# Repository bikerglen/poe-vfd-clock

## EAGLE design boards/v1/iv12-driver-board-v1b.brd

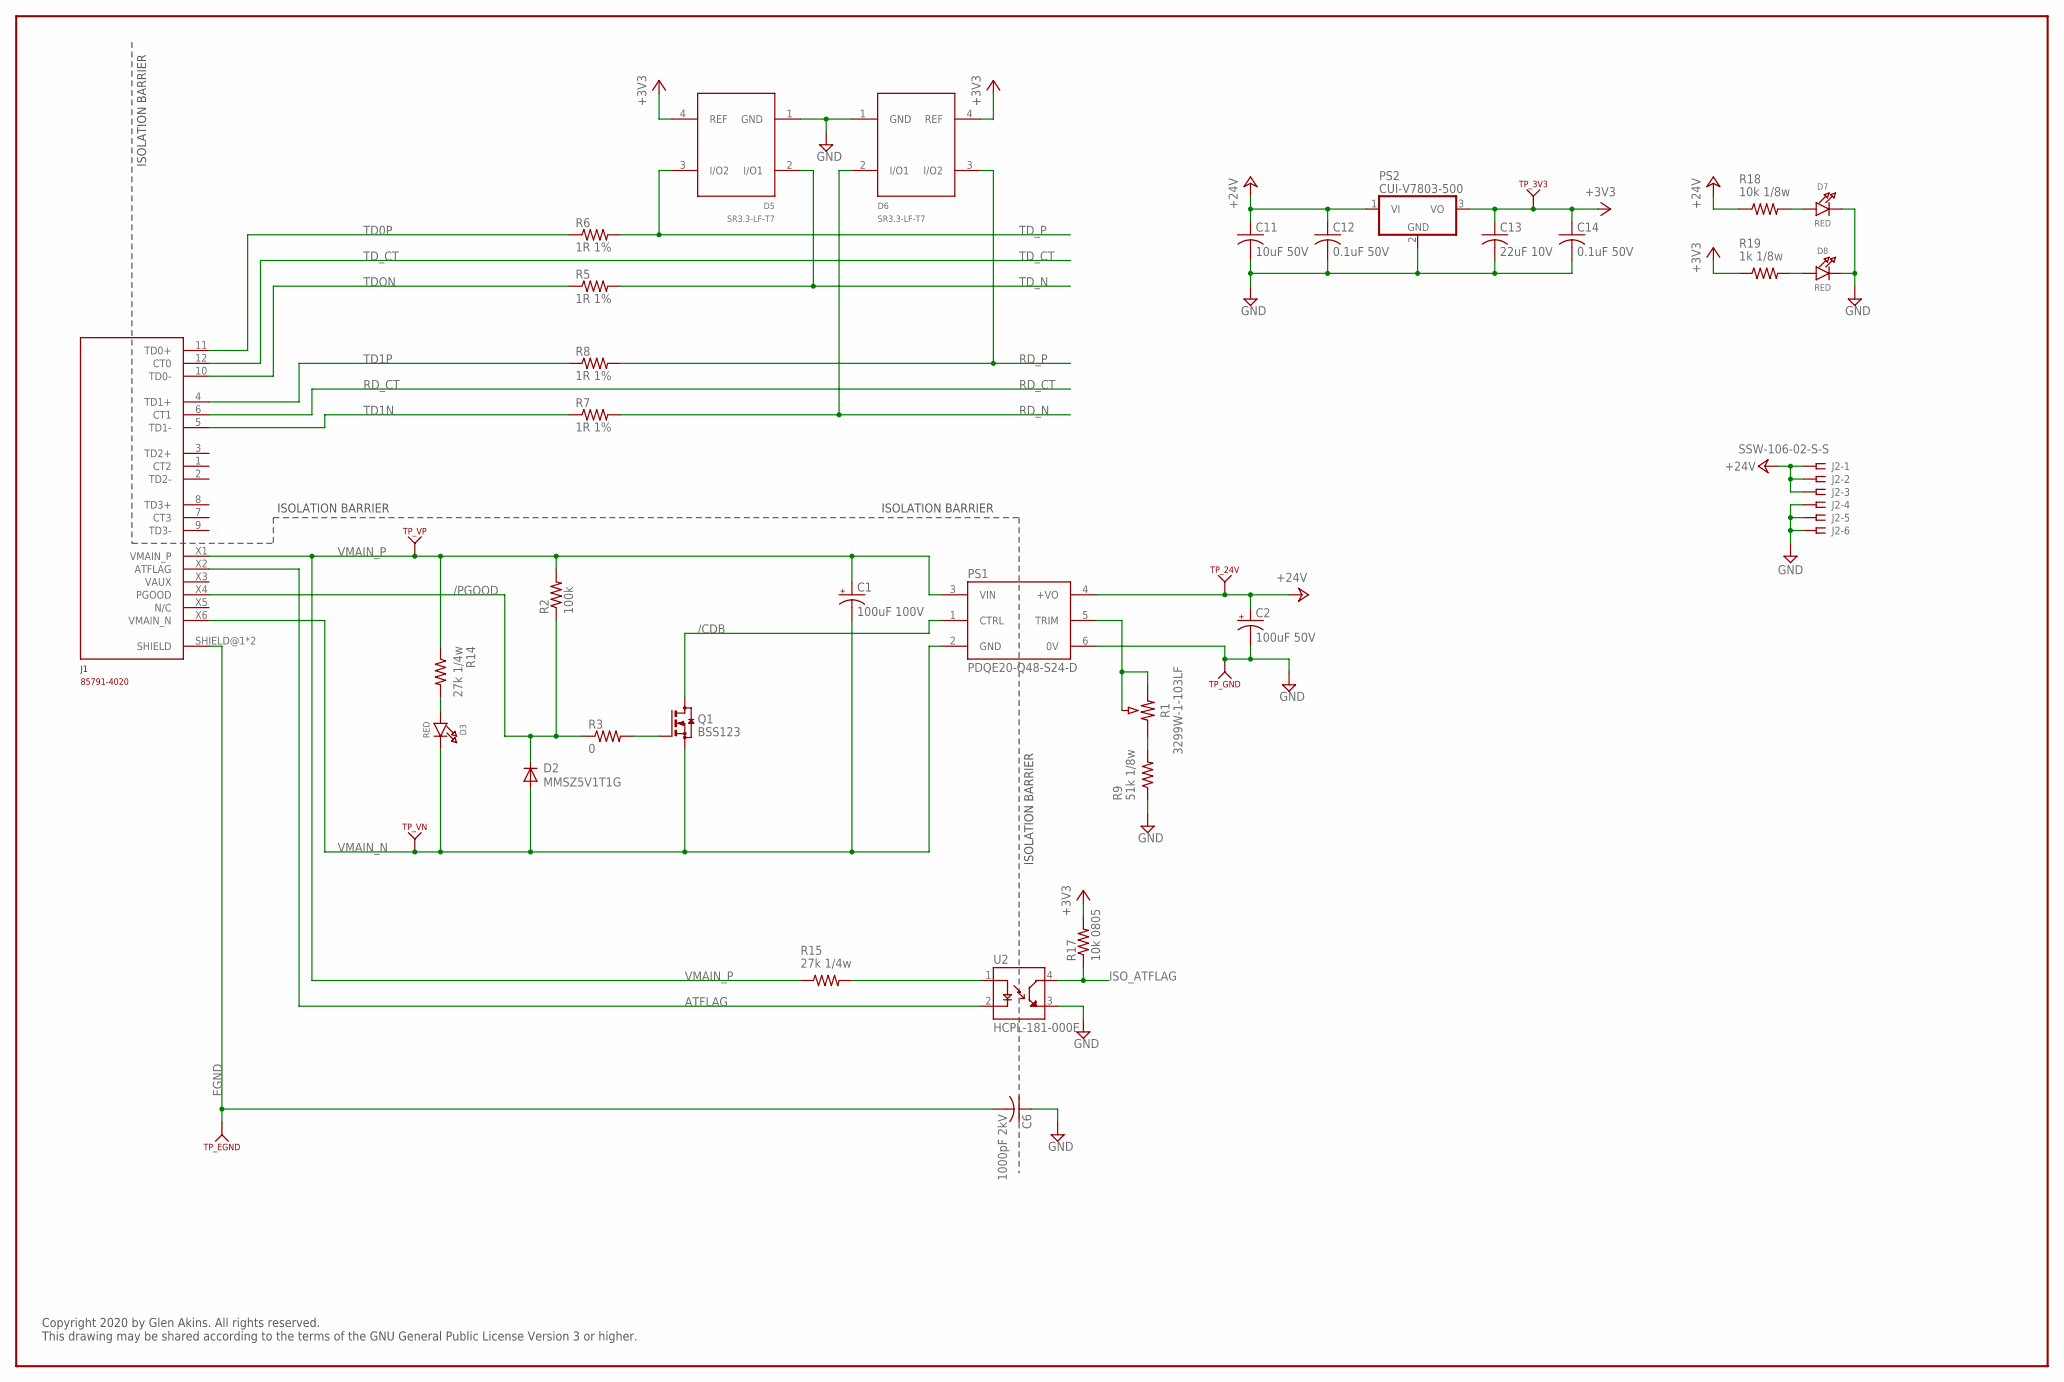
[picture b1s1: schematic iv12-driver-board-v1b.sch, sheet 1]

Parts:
C1: 100uF 100V; E5-13
C2: 100uF 50V; E5-10,5
C6: 1000pF 2kV; C1206K
C11: 10uF 50V; C1210K; MFR_PART_NO C1210C106K5RACTU
C12, C14: 0.1uF 50V; C0805; MFR_PART_NO C1206S104M5RACTU
C13: 22uF 10V; C1206K; MFR_PART_NO C1206C226K8RAC7800
D2: MMSZ5V1T1G; SOD123
D3, D7, D8: RED; CHIPLED_0805_NOOUTLINE
D5, D6: SR3.3-LF-T7; SOT143B
J1: 85791-4020; 85791-X020
J2: SSW-106-02-S-S
PS1: PDQE20-Q48-S24-D; CONV_PDQE20-Q48-S5-D
PS2: CUI-V7803-500; CUI-78XX-500
Q1: BSS123; SOT23
R1: 3299W-1-103LF; POT_3299W
R2: 100k; R0805
R3: 0; R0805
R5, R6, R7, R8: 1R 1%; R0805
R9: 51k 1/8w; R0805
R14, R15: 27k 1/4w; R1206
R17: 10k 0805; R0805
R18: 10k 1/8w; R0805
R19: 1k 1/8w; R0805
TP_3V3, TP_24V: KEYSTONE_500X; KEYSTONE_TP500X
TP_EGND: KEYSTONE_500X; KEYSTONE_TP500X
TP_GND: KEYSTONE_500X; KEYSTONE_TP500X
TP_VN: KEYSTONE_500X; KEYSTONE_TP500X
TP_VP: KEYSTONE_500X; KEYSTONE_TP500X
U2: HCPL-181-000E; SOIC254P675X240-4N

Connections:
+3V3: C13.1, C14.1, D5.4 (REF), D6.4 (REF), PS2.3 (VO), R17.2, R19.1, TP_3V3.1; also elsewhere on the board
+24V: C2.+, C11.1, C12.1, J2.1, J2.2, J2.3, PS1.4 (+VO), PS2.1 (VI), R18.1, TP_24V.1
/CDB: PS1.1 (CTRL), Q1.3 (D)
/PGOOD: D2.C, J1.X4 (PGOOD), R2.1, R3.1
ATFLAG: J1.X2 (ATFLAG), U2.2 (CATHODE)
EGND: C6.2, J1.SHIELD@1 (SHIELD), J1.SHIELD@2 (SHIELD), TP_EGND.1
GND: C2.-, C6.1, C11.2, C12.2, C13.2, C14.2, D5.1 (GND), D6.1 (GND), D7.C, D8.C, J2.4, J2.5, J2.6, PS1.6 (0V), PS2.2 (GND), R9.1, TP_GND.1, U2.3 (EMITTER); also elsewhere on the board
ISO_ATFLAG: R17.1, U2.4 (COLLECTOR); also elsewhere on the board
unnamed: R1.1, R9.2
unnamed: R15.2, U2.1 (ANODE)
unnamed: Q1.1 (G), R3.2
unnamed: D3.A, R14.2
unnamed: D7.A, R18.2
unnamed: D8.A, R19.2
RD_CT: J1.6 (CT1); also elsewhere on the board
RD_N: D6.2 (I/O1), R7.2; also elsewhere on the board
RD_P: D6.3 (I/O2), R8.2; also elsewhere on the board
TD0P: J1.11 (TD0+), R6.1
TD1N: J1.5 (TD1-), R7.1
TD1P: J1.4 (TD1+), R8.1
TDON: J1.10 (TD0-), R5.1
TD_CT: J1.12 (CT0); also elsewhere on the board
TD_N: D5.2 (I/O1), R5.2; also elsewhere on the board
TD_P: D5.3 (I/O2), R6.2; also elsewhere on the board
V24ADJ: PS1.5 (TRIM), R1.2, R1.3
VMAIN_N: C1.-, D2.A, D3.C, J1.X6 (VMAIN_N), PS1.2 (GND), Q1.2 (S), TP_VN.1
VMAIN_P: C1.+, J1.X1 (VMAIN_P), PS1.3 (VIN), R2.2, R14.1, R15.1, TP_VP.1

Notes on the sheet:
ISOLATION BARRIER
Copyright 2020 by Glen Akins. All rights reserved. This drawing may be shared according to the terms of the GNU General Public License Version 3 or higher.

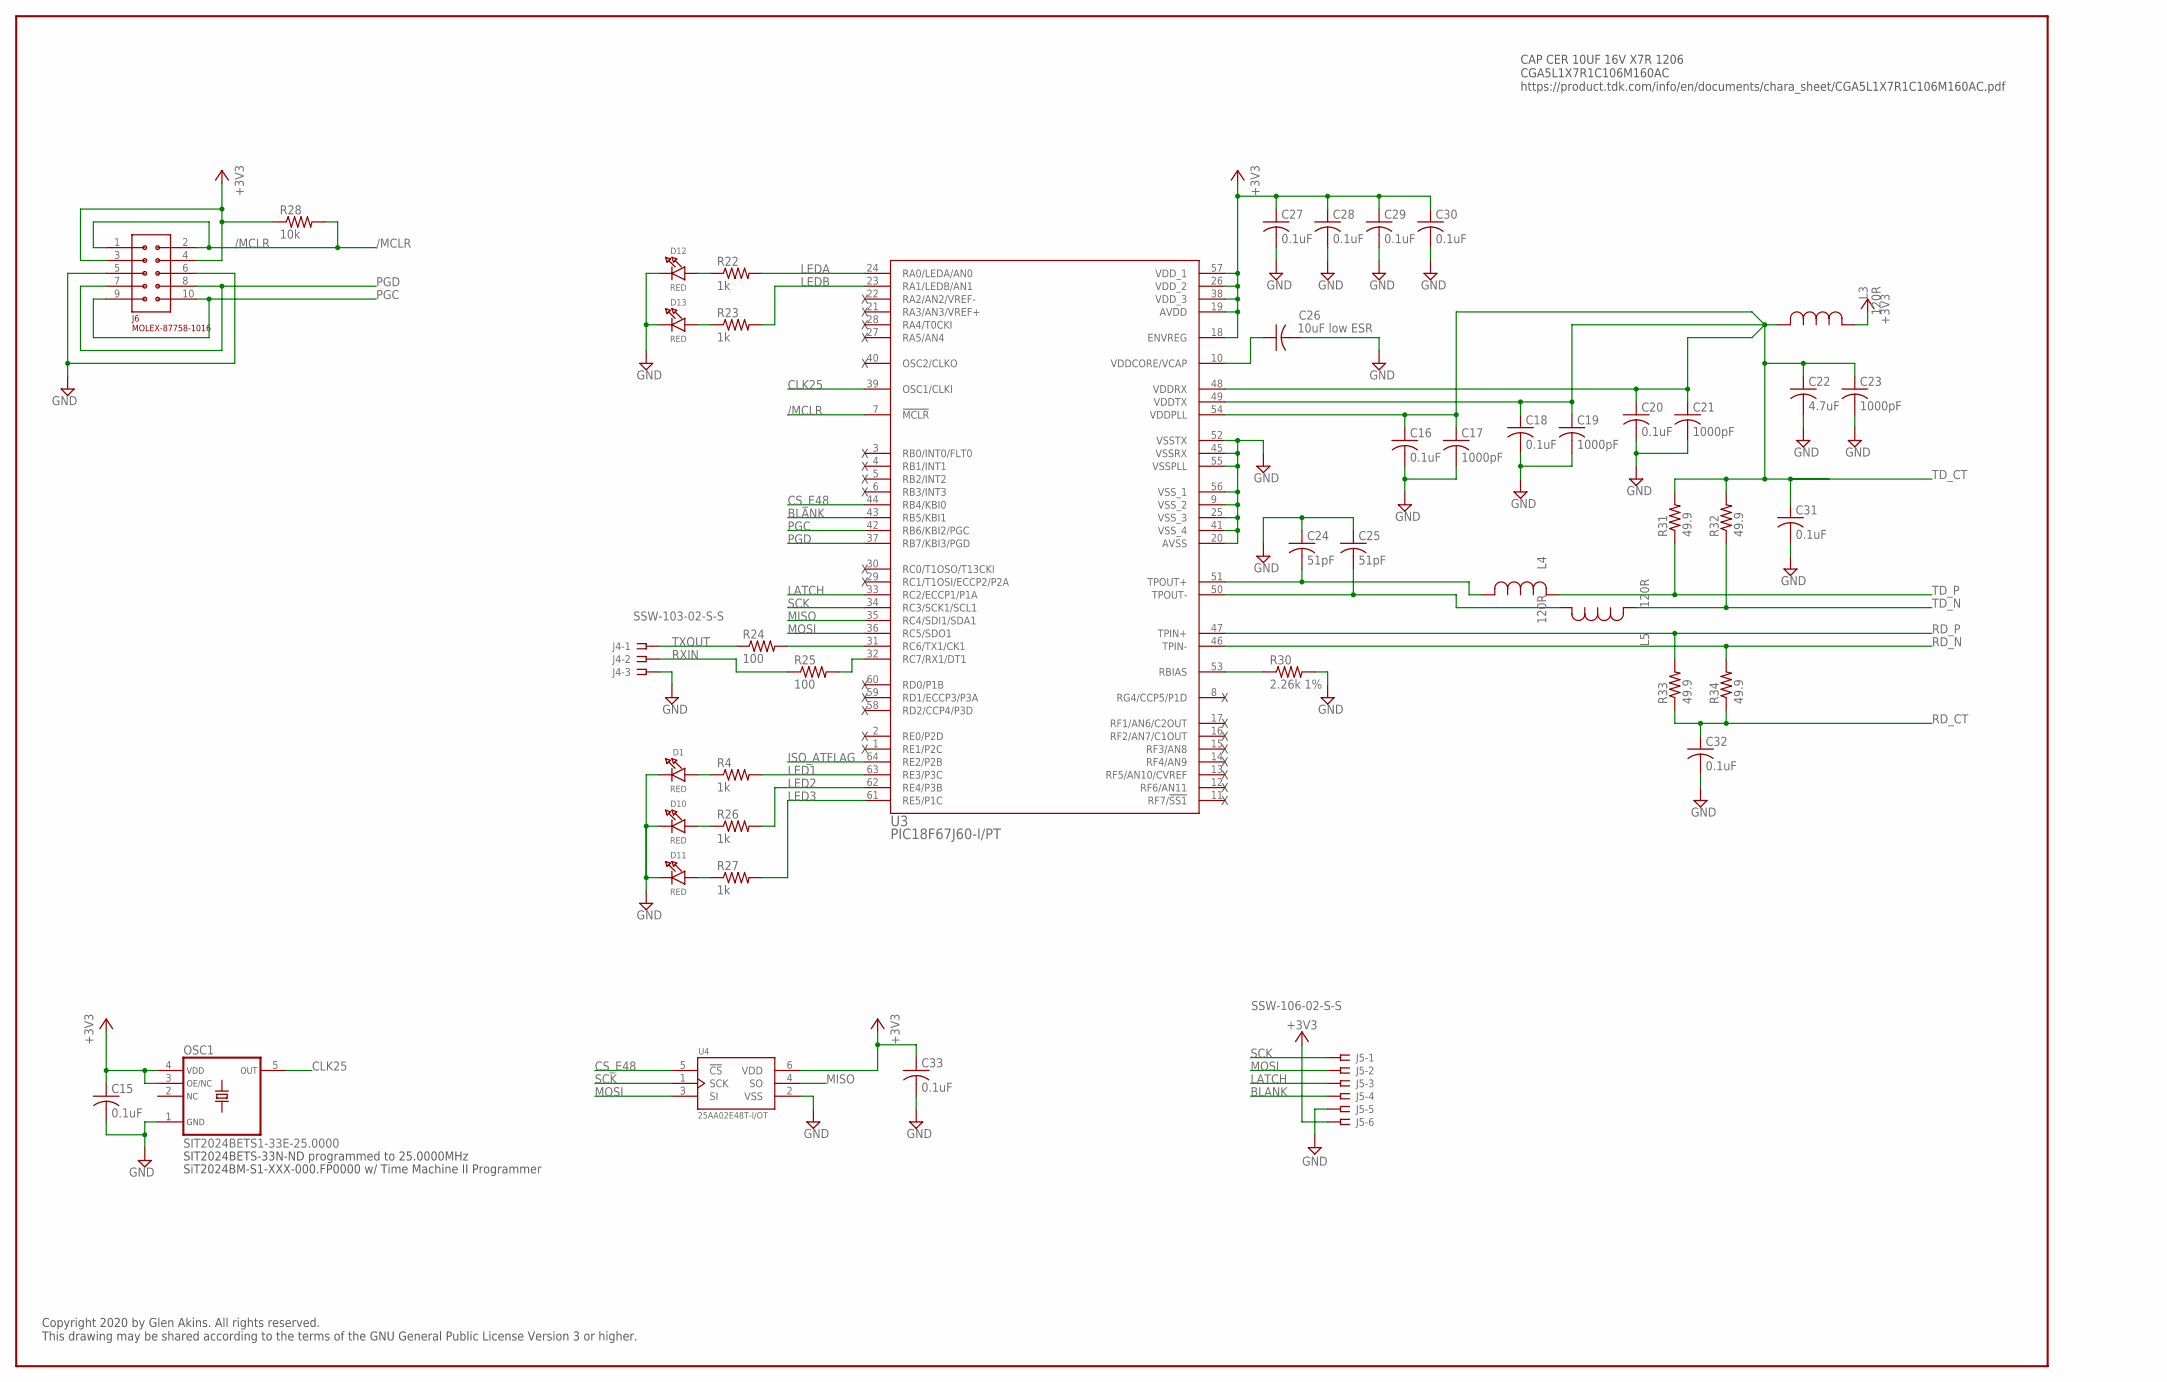
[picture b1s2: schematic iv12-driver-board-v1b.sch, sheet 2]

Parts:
C15, C27, C28, C29, C30, C33: 0.1uF; C0603
C16, C18, C20, C31, C32: 0.1uF; C0805
C17, C19, C21, C23: 1000pF; C0805
C22: 4.7uF; C0805
C24, C25: 51pF; C0805
C26: 10uF low ESR; C1206
D1, D10, D11, D12, D13: RED; CHIPLED_0805_NOOUTLINE
J4: SSW-103-02-S-S
J5: SSW-106-02-S-S
J6: MOLEX-87758-1016; CON-2MM-2X5; MFR_PART_NO 87758-1016
L3, L4, L5: 120R; IND_1608-M
OSC1: SIT2024BETS1-33E-25.0000; SOT23-5
R4, R22, R23, R26, R27: 1k; R0805
R24, R25: 100; R0805
R28: 10k; R0805
R30: 2.26k 1%; R0805
R31, R32, R33, R34: 49.9; R0805
U3: PIC18F67J60-I/PT; TQFP64_10X10MC
U4: 25AA02E48T-I/OT; SOT95P270X145-6N

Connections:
+3V3: C15.1, C27.1, C28.1, C29.1, C30.1, C33.1, J5.6, J6.3, J6.4, L3.2, OSC1.3 (OE/NC), OSC1.4 (VDD), R28.1, U3.18 (ENVREG), U3.19 (AVDD), U3.26 (VDD_2), U3.38 (VDD_3), U3.57 (VDD_1), U4.6 (VDD); also elsewhere on the board
/MCLR: J6.1, J6.2, R28.2, U3.7 (!MCLR)
BLANK: J5.4, U3.43 (RB5/KBI1)
CLK25: OSC1.5 (OUT), U3.39 (OSC1/CLKI)
CS_E48: U3.44 (RB4/KBI0), U4.5 (!CS)
GND: C15.2, C16.2, C17.2, C18.2, C19.2, C20.2, C21.2, C22.2, C23.2, C24.1, C25.1, C26.2, C27.2, C28.2, C29.2, C30.2, C31.2, C32.2, C33.2, D1.C, D10.C, D11.C, D12.C, D13.C, J4.3, J5.5, J6.5, J6.6, OSC1.1 (GND), R30.2, U3.9 (VSS_2), U3.20 (AVSS), U3.25 (VSS_3), U3.41 (VSS_4), U3.45 (VSSRX), U3.52 (VSSTX), U3.55 (VSSPLL), U3.56 (VSS_1), U4.2 (VSS); also elsewhere on the board
ISO_ATFLAG: U3.64 (RE2/P2B); also elsewhere on the board
LATCH: J5.3, U3.33 (RC2/ECCP1/P1A)
LED1: R4.2, U3.63 (RE3/P3C)
LED2: R26.2, U3.62 (RE4/P3B)
LED3: R27.2, U3.61 (RE5/P1C)
LEDA: R22.2, U3.24 (RA0/LEDA/AN0)
LEDB: R23.2, U3.23 (RA1/LEDB/AN1)
MISO: U3.35 (RC4/SDI1/SDA1), U4.4 (SO)
MOSI: J5.2, U3.36 (RC5/SDO1), U4.3 (SI)
unnamed: D1.A, R4.1
unnamed: R30.1, U3.53 (RBIAS)
unnamed: D13.A, R23.1
unnamed: D10.A, R26.1
unnamed: D11.A, R27.1
unnamed: D12.A, R22.1
PGC: J6.9, J6.10, U3.42 (RB6/KBI2/PGC)
PGD: J6.7, J6.8, U3.37 (RB7/KBI3/PGD)
RD_CT: C32.1, R33.1, R34.1; also elsewhere on the board
RD_N: R34.2, U3.46 (TPIN-); also elsewhere on the board
RD_P: R33.2, U3.47 (TPIN+); also elsewhere on the board
RXD: R25.2, U3.32 (RC7/RX1/DT1)
RXIN: J4.2, R25.1
SCK: J5.1, U3.34 (RC3/SCK1/SCL1), U4.1 (SCK)
TDF_N: C25.2, L5.1, U3.50 (TPOUT-)
TDF_P: C24.2, L4.1, U3.51 (TPOUT+)
TD_CT: C16.1, C17.1, C18.1, C19.1, C20.1, C21.1, C22.1, C23.1, C31.1, L3.1, R31.2, R32.2, U3.48 (VDDRX), U3.49 (VDDTX), U3.54 (VDDPLL); also elsewhere on the board
TD_N: L5.2, R32.1; also elsewhere on the board
TD_P: L4.2, R31.1; also elsewhere on the board
TXD: R24.2, U3.31 (RC6/TX1/CK1)
TXOUT: J4.1, R24.1
VCAP: C26.1, U3.10 (VDDCORE/VCAP)

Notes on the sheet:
SIT2024BETS-33N-ND programmed to 25.0000MHz
SiT2024BM-S1-XXX-000.FP0000 w/ Time Machine II Programmer
CAP CER 10UF 16V X7R 1206 CGA5L1X7R1C106M160AC https://product.tdk.com/info/en/documents/chara_sheet/CGA5L1X7R1C106M160AC.pdf
Copyright 2020 by Glen Akins. All rights reserved. This drawing may be shared according to the terms of the GNU General Public License Version 3 or higher.

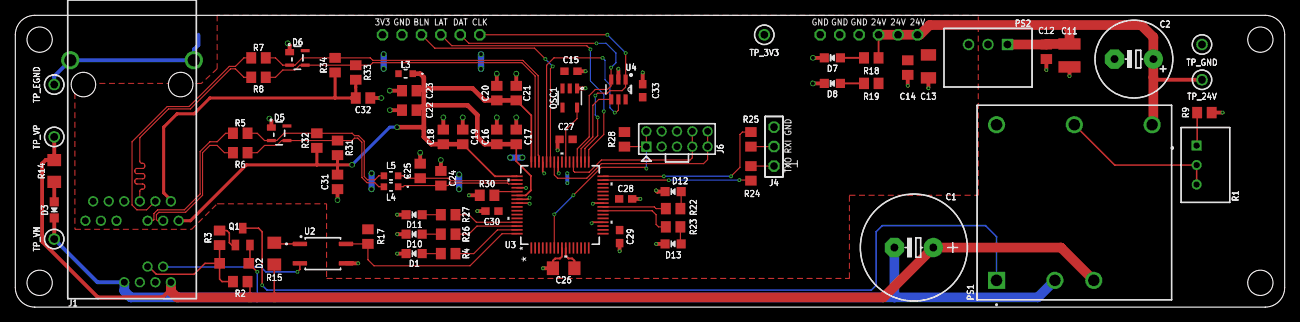
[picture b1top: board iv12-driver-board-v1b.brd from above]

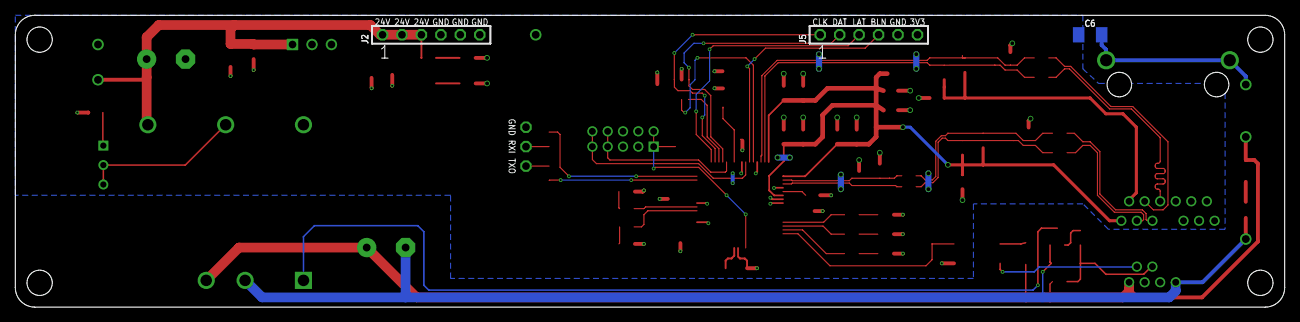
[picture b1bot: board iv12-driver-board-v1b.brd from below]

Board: 2 copper layers, 165.7 x 38.1 mm, 84 parts (3 on the bottom side), 55 nets.

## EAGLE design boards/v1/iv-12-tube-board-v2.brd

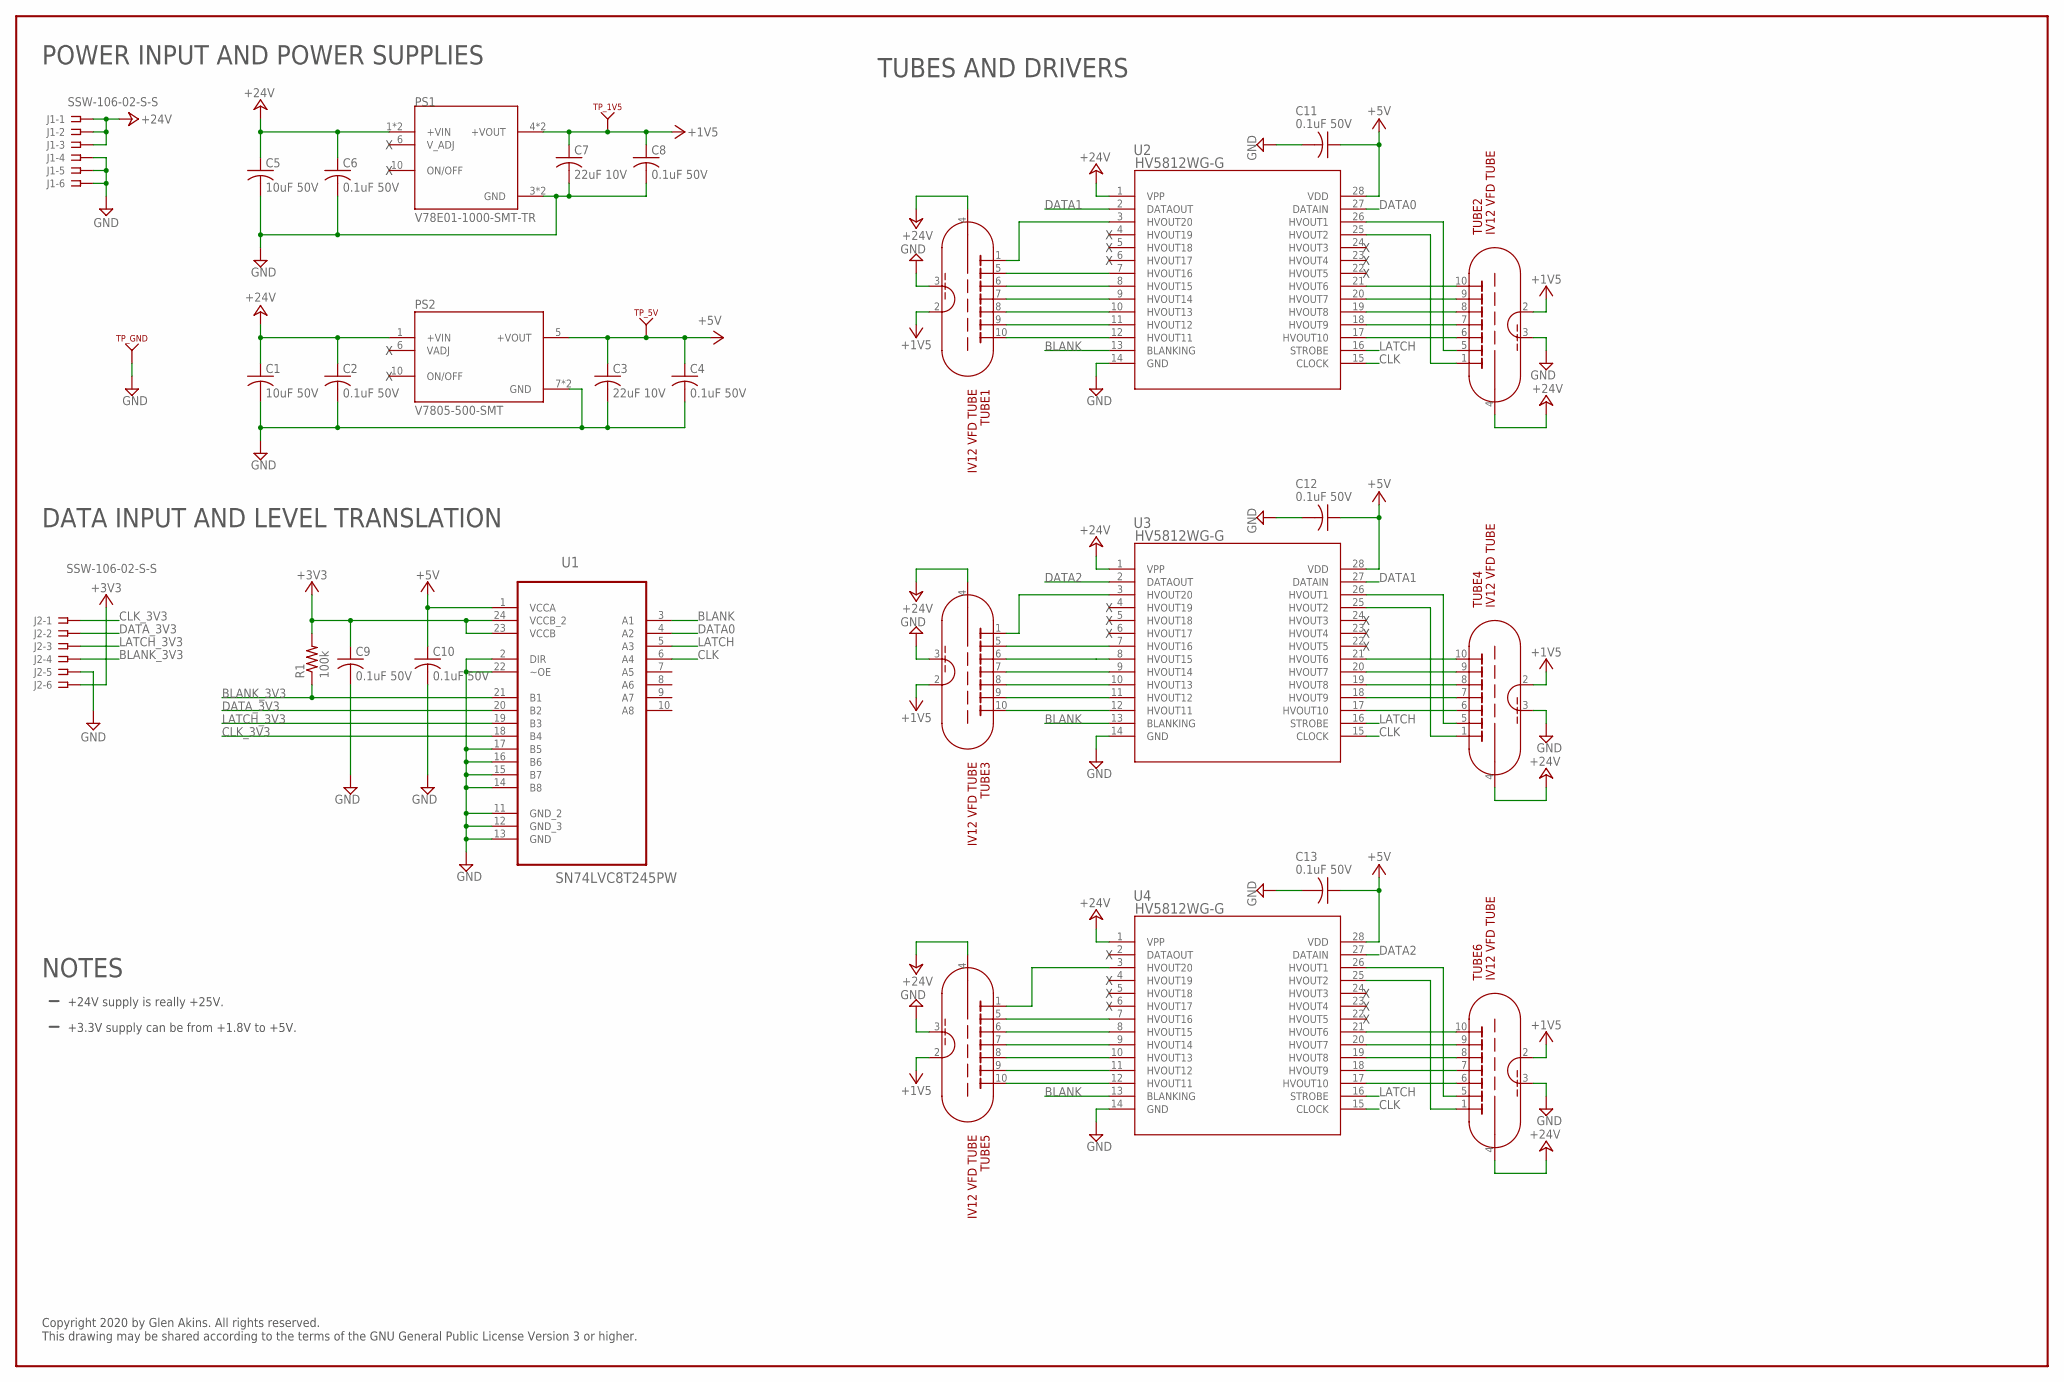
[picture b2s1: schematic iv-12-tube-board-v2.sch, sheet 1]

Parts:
C1, C5: 10uF 50V; C1210K; MFR_PART_NO C1210C106K5RACTU
C2, C4, C6, C8: 0.1uF 50V; C1206K; MFR_PART_NO C1206S104M5RACTU
C3, C7: 22uF 10V; C1206K; MFR_PART_NO C1206C226K8RAC7800
C9, C10: 0.1uF 50V; C0805K
C11, C12, C13: 0.1uF 50V; C0805
J1, J2: SSW-106-02-S-S
PS1: V78E01-1000-SMT-TR; CONV_V78E01-1000-SMT-TR
PS2: V7805-500-SMT; CONV_V7805-500-SMT
R1: 100k; R0805
TP_1V5, TP_5V: KEYSTONE_500X; KEYSTONE_TP500X
TP_GND: KEYSTONE_500X; KEYSTONE_TP500X
TUBE1, TUBE2, TUBE3, TUBE4, TUBE5, TUBE6: IV12 VFD TUBE; IV-12-VFD-TUBE-11.9MM-10PIN-34DEG
U1: SN74LVC8T245PW; SOP65P640X120-24N
U2, U3, U4: HV5812WG-G; SOW28_17P90X7P50

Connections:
+1V5: C7.1, C8.1, PS1.4 (+VOUT), PS1.5 (+VOUT), TP_1V5.1, TUBE1.2, TUBE2.2, TUBE3.2, TUBE4.2, TUBE5.2, TUBE6.2
+3V3: C9.1, J2.6, R1.2, U1.23 (VCCB), U1.24 (VCCB_2)
+5V: C3.1, C4.1, C10.1, C11.1, C12.1, C13.1, PS2.5 (+VOUT), TP_5V.1, U1.1 (VCCA), U2.28 (VDD), U3.28 (VDD), U4.28 (VDD)
+24V: C1.1, C2.1, C5.1, C6.1, J1.1, J1.2, J1.3, PS1.1 (+VIN), PS1.2 (+VIN), PS2.1 (+VIN), TUBE1.4, TUBE2.4, TUBE3.4, TUBE4.4, TUBE5.4, TUBE6.4, U2.1 (VPP), U3.1 (VPP), U4.1 (VPP)
BLANK: U1.3 (A1), U2.13 (BLANKING), U3.13 (BLANKING), U4.13 (BLANKING)
BLANK_3V3: J2.4, R1.1, U1.21 (B1)
CLK: U1.6 (A4), U2.15 (CLOCK), U3.15 (CLOCK), U4.15 (CLOCK)
CLK_3V3: J2.1, U1.18 (B4)
DATA0: U1.4 (A2), U2.27 (DATAIN)
DATA1: U2.2 (DATAOUT), U3.27 (DATAIN)
DATA2: U3.2 (DATAOUT), U4.27 (DATAIN)
DATA_3V3: J2.2, U1.20 (B2)
GND: C1.2, C2.2, C3.2, C4.2, C5.2, C6.2, C7.2, C8.2, C9.2, C10.2, C11.2, C12.2, C13.2, J1.4, J1.5, J1.6, J2.5, PS1.3 (GND), PS1.7 (GND), PS2.7 (GND), PS2.9 (GND), TP_GND.1, TUBE1.3, TUBE2.3, TUBE3.3, TUBE4.3, TUBE5.3, TUBE6.3, U1.2 (DIR), U1.11 (GND_2), U1.12 (GND_3), U1.13 (GND), U1.14 (B8), U1.15 (B7), U1.16 (B6), U1.17 (B5), U1.22 (~OE), U2.14 (GND), U3.14 (GND), U4.14 (GND)
LATCH: U1.5 (A3), U2.16 (STROBE), U3.16 (STROBE), U4.16 (STROBE)
LATCH_3V3: J2.3, U1.19 (B3)
unnamed: TUBE1.1, U2.3 (HVOUT20)
unnamed: TUBE1.10, U2.12 (HVOUT11)
unnamed: TUBE1.9, U2.11 (HVOUT12)
unnamed: TUBE1.8, U2.10 (HVOUT13)
unnamed: TUBE1.7, U2.9 (HVOUT14)
unnamed: TUBE1.6, U2.8 (HVOUT15)
unnamed: TUBE1.5, U2.7 (HVOUT16)
unnamed: TUBE2.1, U2.25 (HVOUT2)
unnamed: TUBE2.5, U2.26 (HVOUT1)
unnamed: TUBE2.6, U2.17 (HVOUT10)
unnamed: TUBE2.7, U2.18 (HVOUT9)
unnamed: TUBE2.8, U2.19 (HVOUT8)
unnamed: TUBE2.9, U2.20 (HVOUT7)
unnamed: TUBE2.10, U2.21 (HVOUT6)
unnamed: TUBE3.1, U3.3 (HVOUT20)
unnamed: TUBE5.1, U4.3 (HVOUT20)
unnamed: TUBE3.5, U3.7 (HVOUT16)
unnamed: TUBE3.6, U3.8 (HVOUT15)
unnamed: TUBE3.7, U3.9 (HVOUT14)
unnamed: TUBE3.8, U3.10 (HVOUT13)
unnamed: TUBE3.9, U3.11 (HVOUT12)
unnamed: TUBE3.10, U3.12 (HVOUT11)
unnamed: TUBE5.10, U4.12 (HVOUT11)
unnamed: TUBE5.9, U4.11 (HVOUT12)
unnamed: TUBE5.8, U4.10 (HVOUT13)
unnamed: TUBE5.7, U4.9 (HVOUT14)
unnamed: TUBE5.6, U4.8 (HVOUT15)
unnamed: TUBE5.5, U4.7 (HVOUT16)
unnamed: TUBE4.5, U3.26 (HVOUT1)
unnamed: TUBE4.1, U3.25 (HVOUT2)
unnamed: TUBE4.10, U3.21 (HVOUT6)
unnamed: TUBE4.9, U3.20 (HVOUT7)
unnamed: TUBE4.8, U3.19 (HVOUT8)
unnamed: TUBE4.7, U3.18 (HVOUT9)
unnamed: TUBE4.6, U3.17 (HVOUT10)
unnamed: TUBE6.6, U4.17 (HVOUT10)
unnamed: TUBE6.7, U4.18 (HVOUT9)
unnamed: TUBE6.8, U4.19 (HVOUT8)
unnamed: TUBE6.9, U4.20 (HVOUT7)
unnamed: TUBE6.10, U4.21 (HVOUT6)
unnamed: TUBE6.5, U4.26 (HVOUT1)
unnamed: TUBE6.1, U4.25 (HVOUT2)

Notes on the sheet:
POWER INPUT AND POWER SUPPLIES
DATA INPUT AND LEVEL TRANSLATION
TUBES AND DRIVERS
NOTES
+24V supply is really +25V.
+3.3V supply can be from +1.8V to +5V.
Copyright 2020 by Glen Akins. All rights reserved. This drawing may be shared according to the terms of the GNU General Public License Version 3 or higher.

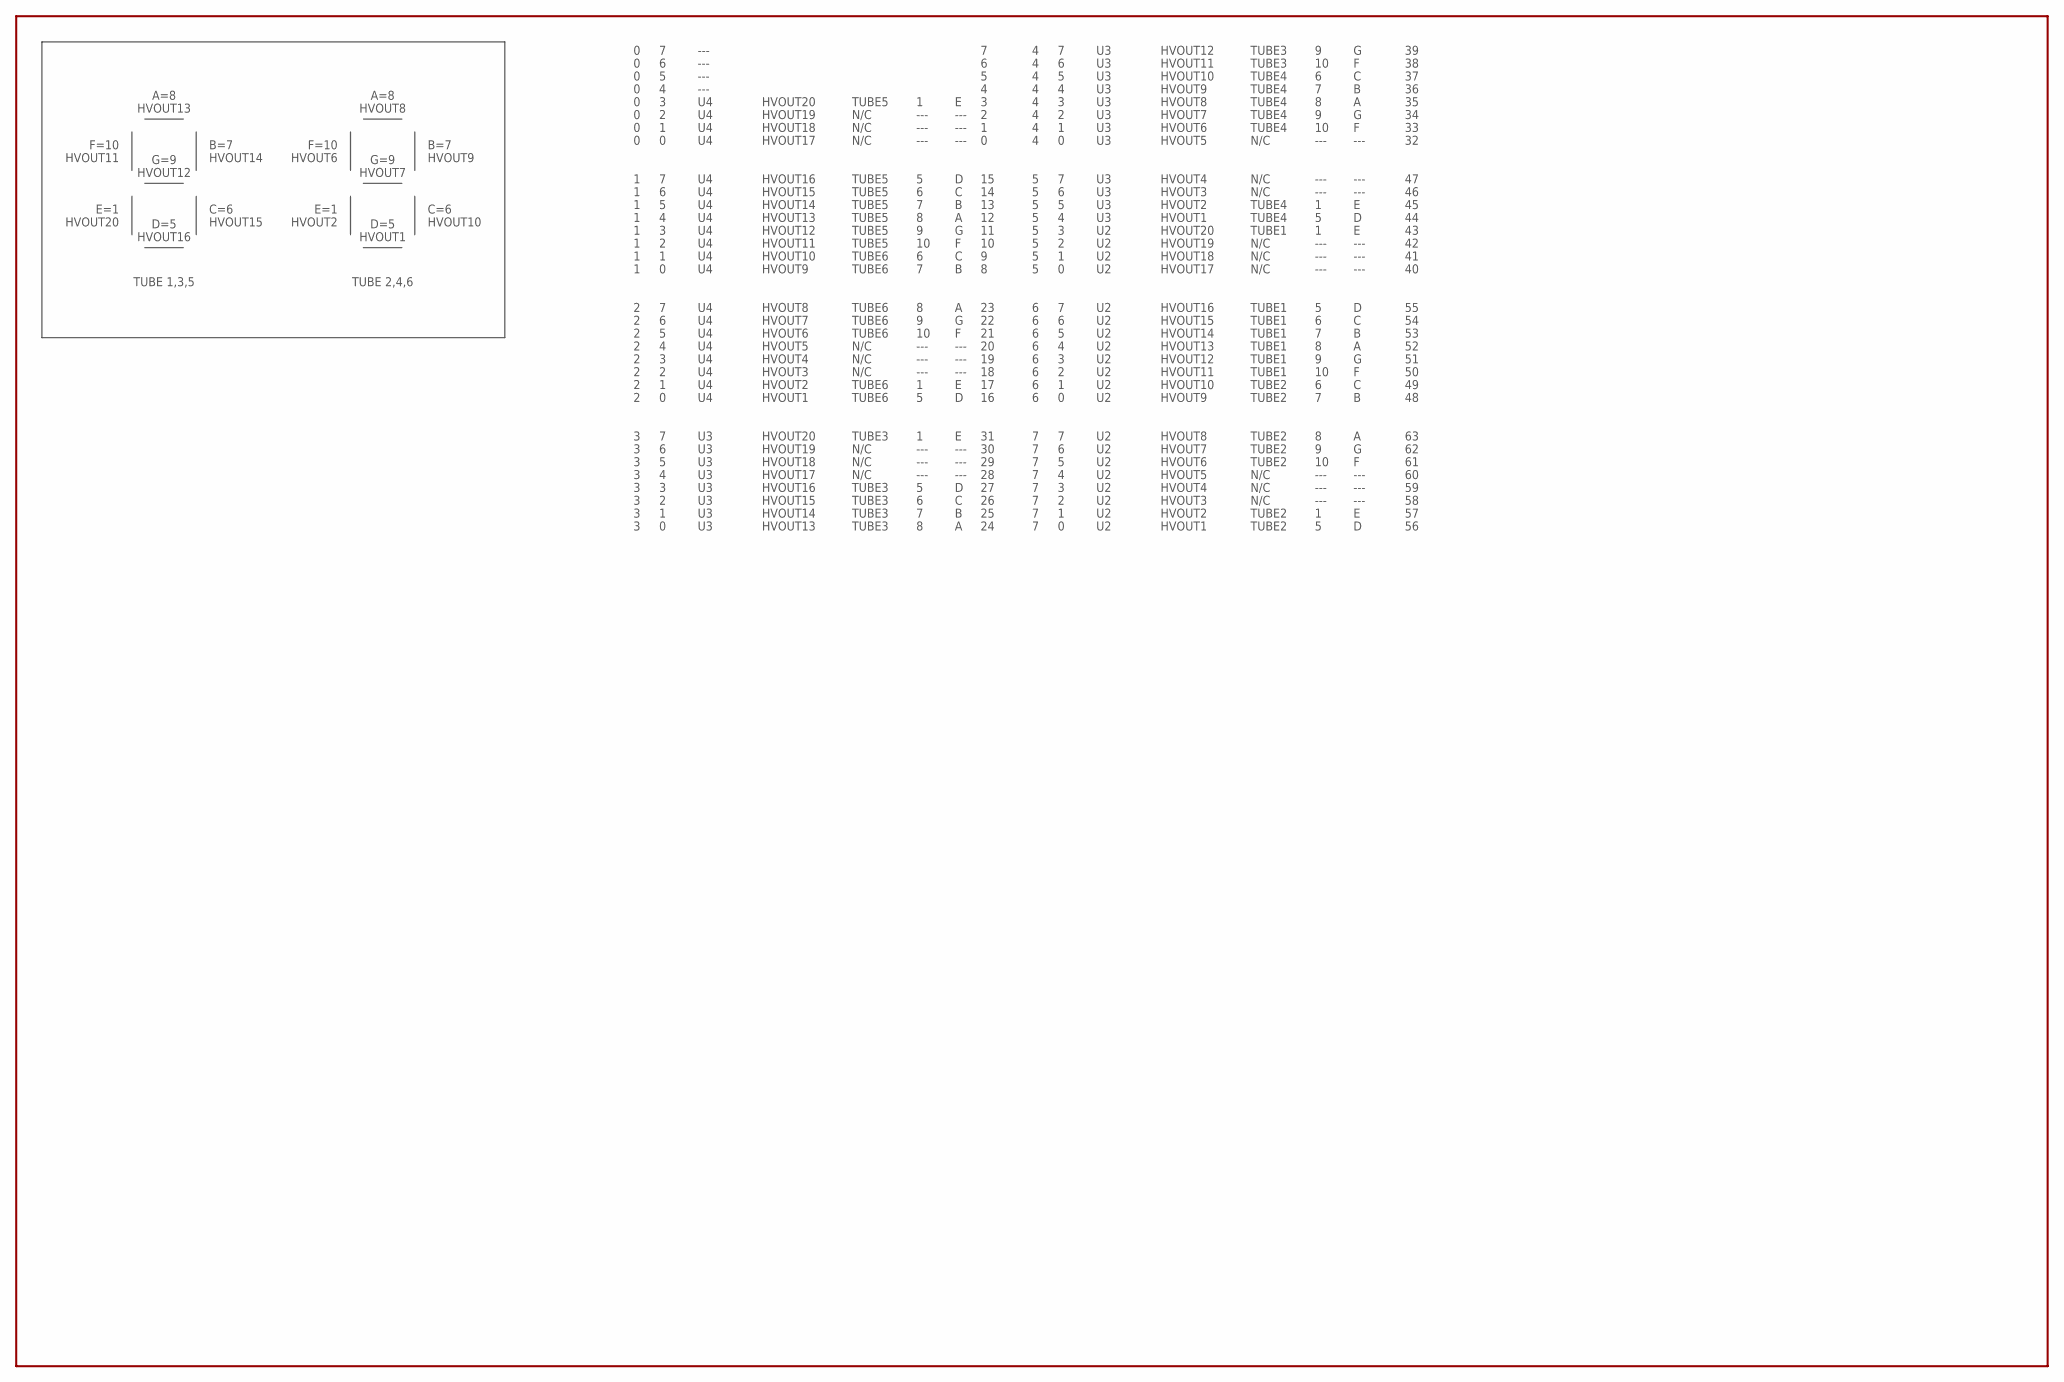
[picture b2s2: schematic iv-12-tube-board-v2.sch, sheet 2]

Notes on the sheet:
A=8
B=7
C=6
D=5
E=1
F=10
G=9
HVOUT1
HVOUT2
HVOUT6
HVOUT7
HVOUT8
HVOUT9
HVOUT10
HVOUT16
HVOUT20
HVOUT11
HVOUT12
HVOUT13
HVOUT14
HVOUT15
TUBE 2,4,6
TUBE 1,3,5
HVOUT4
HVOUT3
HVOUT5
HVOUT17
HVOUT18
HVOUT19
TUBE2
TUBE1
N/C
---
TUBE4
TUBE3
TUBE6
TUBE5

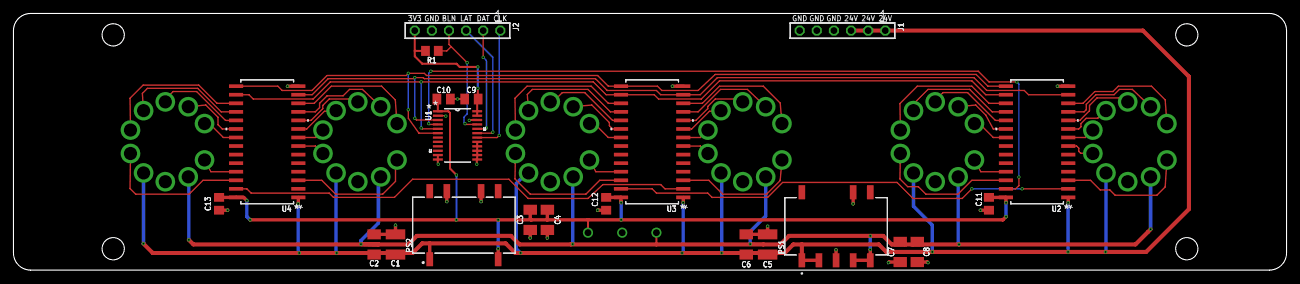
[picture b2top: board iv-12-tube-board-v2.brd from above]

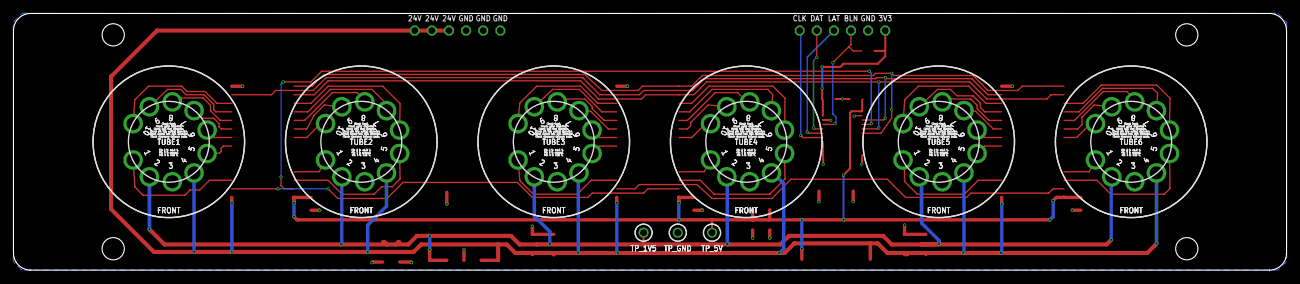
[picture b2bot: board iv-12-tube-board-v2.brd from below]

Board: 2 copper layers, 189.0 x 38.1 mm, 31 parts (9 on the bottom side), 57 nets.

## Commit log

2020-01-12 initial checkin
2020-01-13 changed to correct version of board

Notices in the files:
parts and their libraries:
COPYRIGHT: Copyright (C) 2018 Accelerated Designs. All rights reserved
microbuilder: This work is placed in the public domain, and may be freely used for commercial and non-commercial work with the following conditions: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
